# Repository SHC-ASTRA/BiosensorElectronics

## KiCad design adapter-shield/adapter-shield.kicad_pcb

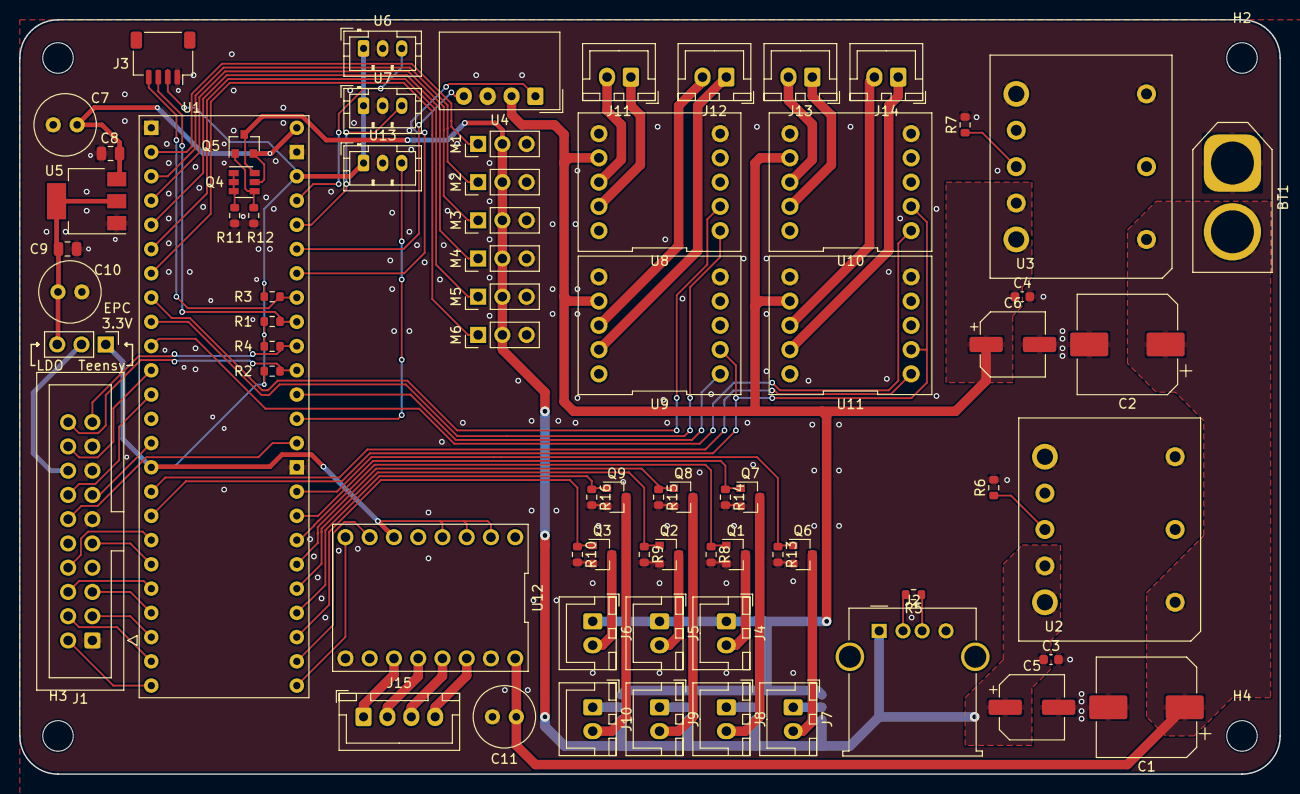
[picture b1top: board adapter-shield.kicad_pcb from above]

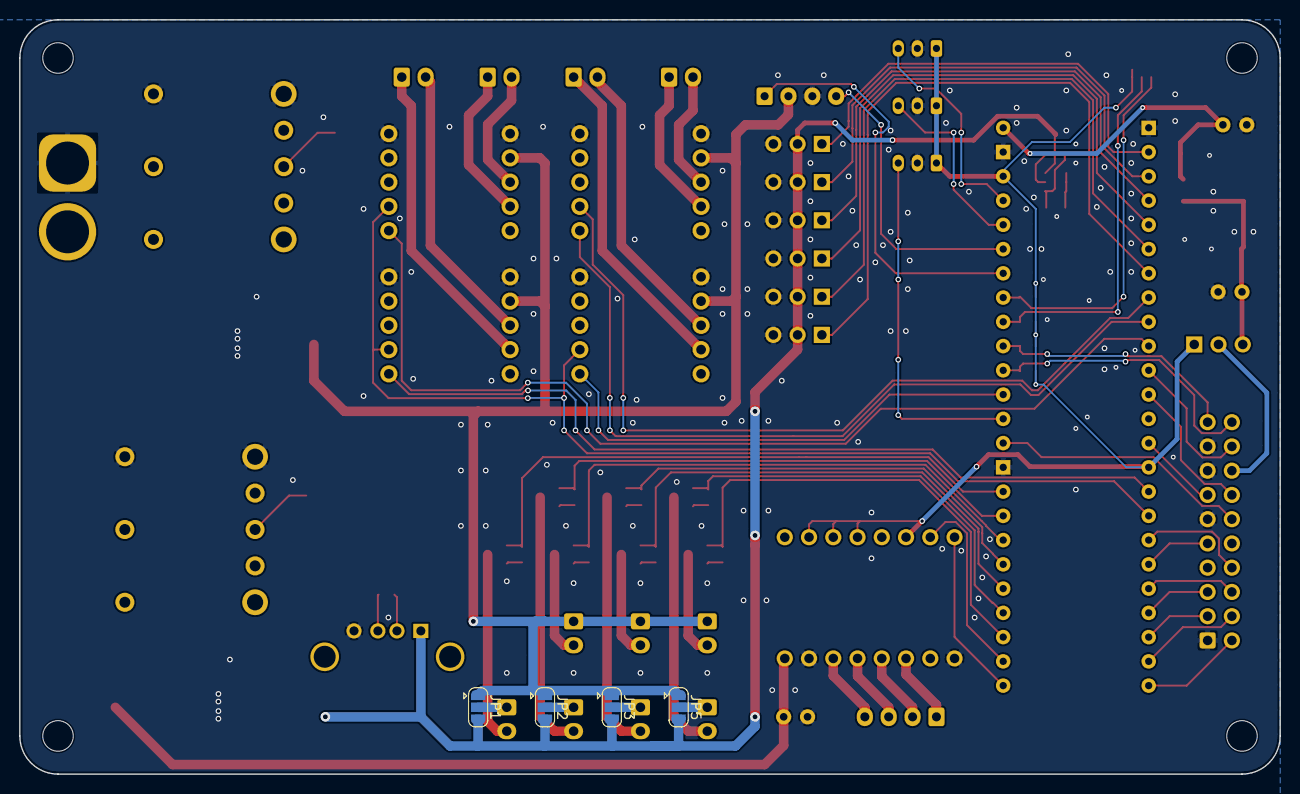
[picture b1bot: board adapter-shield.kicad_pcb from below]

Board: 2 copper layers, 132.0 x 79.0 mm, 80 parts (4 on the bottom side), 78 nets.

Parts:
BT1: XT60_Battery_Connector; AMASS_XT60-M_1x02_P7.20mm_Vertical
C1, C2: 33u; CP_Elec_10x10
C3, C4: 0.1u; C_0603_1608Metric
C5, C6: 22u; CP_Elec_6.3x5.9
C7, C10, C11: 100uF; C_Radial_D6.3mm_H7.0mm_P2.50mm
C8, C9: 1uF; C_0805_2012Metric
H1, H2, H3, H4: MountingHole; MountingHole_3.2mm_M3
J1: Camera; IDC-Header_2x10_P2.54mm_Vertical
J2: USB_A; USB_A_Molex_67643_Horizontal
J3: QWIIC_Generic_Conn; JST_SH_SM04B-SRSS-TB_1x04-1MP_P1.00mm_Horizontal
J4, J5, J6, J7, J8, J9, J10, J11, J12, J13, J14: Conn_01x02; JST_XH_B2B-XH-A_1x02_P2.50mm_Vertical
J15: Conn_01x04; JST_XH_B4B-XH-A_1x04_P2.50mm_Vertical
JP1, JP2, JP3, JP5: SolderJumper_3_Open; SolderJumper-3_P1.3mm_Open_RoundedPad1.0x1.5mm
JP4: Jumper; PinHeader_1x03_P2.54mm_Vertical
M1, M2, M3, M4, M5, M6: Motor_Servo; PinHeader_1x03_P2.54mm_Vertical
Q1, Q2, Q3, Q6, Q7, Q8, Q9: Q_NMOS_GSD; SOT-23
Q4: Q_DUAL_PNP_PNP_C1B1B2C2E2E1; SOT-23-6
Q5: Q_PMOS_GSD; SOT-23
R1, R2, R3, R4, R8, R9, R10, R11, R13, R14, R15, R16: 10k; R_0603_1608Metric
R5: 200; R_0603_1608Metric
R6: 8.45k; R_0603_1608Metric
R7: 1.82k; R_0603_1608Metric
R12: 47k; R_0603_1608Metric
U1: Teensy_4.1; Teensy4.1
U2, U3: TDK_I3A4W008A033V; Power_Supply_32nd_Brick
U4: LynxServo; Molex_SPOX_5268-04A_1x04_P2.50mm_Horizontal
U5: 3.3V LDO; SOT-223-3_TabPin2
U6, U7, U13: AH1815-P-B; JST_PH_B3B-PH-K_1x03_P2.00mm_Vertical
U8, U9, U10, U11: MAX14870_Breakout; Pololu_2961
U12: Pololu_Compact_TB67S249FTG; DIP-16_500

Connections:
+3V3: J3.2, JP4.1, R1.1, R2.1, R3.1, R4.1, U1.15, U1.28, U6.1, U7.1, U12.2, U12.3, U12.4, U12.6, U13.1
+5V: C7.1, C8.1, Q4.5, Q5.2, U1.30, U5.3
+5VP: C3.1, C5.1, J2.1, JP1.3, JP2.3, JP3.3, JP5.3, M1.2, M2.2, M3.2, M4.2, M5.2, M6.2, Q4.6, Q5.3, U2.7, U2.8
+12V: C4.1, C6.1, J4.1, J5.1, J6.1, JP1.1, JP2.1, JP3.1, JP5.1, U3.7, U3.8, U4.2, U8.7, U9.7, U10.7, U11.7
/ADC_CLK: J1.12, U1.17
/ADC_CS: J1.14, U1.12
/ADC_DATA: J1.13, U1.14
/Act_DIR: U1.8, U8.2
/Act_PWM: U1.9, U8.1
/CLR_DATA: J1.4, U1.38
/CLR_PIX: J1.6, U1.35
/DATA_RDY: J1.3, U1.37
/FAN1: Q1.1, R8.1, U1.46
/FAN2: Q2.1, R9.1, U1.44
/FAN3: Q3.1, R10.1, U1.42
/GEN1: Q7.1, R14.1, U1.47
/GEN2: Q8.1, R15.1, U1.45
/GEN3: Q9.1, R16.1, U1.43
/Hall_SW_1: U1.27, U6.3
/Hall_SW_2: U1.26, U7.3
/Hall_SW_3: U1.18, U13.3
/LIGHT: Q6.1, R13.1, U1.48
/Lynx_RX: U1.24, U4.1
/Lynx_TX: U1.25, U4.4
/M1_PWM: M1.1, U1.2
/M2_PWM: M2.1, U1.3
/M3_PWM: M3.1, U1.4
/M4_PWM: M4.1, U1.5
/M5_PWM: M5.1, U1.6
/M6_PWM: M6.1, U1.7
/PWR_DOWN: J1.2, U1.39
/Pump1_PWM: U1.19, U9.1
/Pump2_PWM: U1.10, U10.1
/Pump3_PWM: U1.31, U11.1
/Pump_DIR: U1.32, U9.2, U10.2, U11.2
/QWIIC_SCL: J3.4, R3.2, U1.23
/QWIIC_SDA: J3.3, R1.2, U1.22
/READ: J1.18, U1.11
/SCL: J1.20, R2.2, U1.20
/SDA: J1.19, R4.2, U1.21
/SHUTTER: J1.5, U1.36
/STEP_DIR: U1.40, U12.8
/STEP_STEP: U1.41, U12.7
/VCC_3V3: J1.16, JP4.2
/VIDEO_N: J1.9, U1.34
/VIDEO_P: J1.8, U1.33
/V_BAT: BT1.2, C1.1, C2.1, C11.1, U2.1, U3.1, U12.16
GND: BT1.1, C1.2, C2.2, C3.2, C4.2, C5.2, C6.2, C7.2, C8.2, C9.2, C10.2, C11.2, J1.1, J1.11, J1.15, J1.17, J2.4, J3.1, M1.3, M2.3, M3.3, M4.3, M5.3, M6.3, Q1.2, Q2.2, Q3.2, Q6.2, Q7.2, Q8.2, Q9.2, R6.2, R7.2, R8.2, R9.2, R10.2, R11.2, R12.2, R13.2, R14.2, R15.2, R16.2, U1.1, U1.16, U1.29, U2.3, U2.4, U3.3, U3.4, U4.3, U5.1, U6.2, U7.2, U8.5, U8.6, U9.5, U9.6, U10.5, U10.6, U11.5, U11.6, U12.9, U12.15, U13.2
unnamed: C9.1, C10.1, JP4.3, U5.2
unnamed: J2.2, R5.2
unnamed: J2.3, R5.1
unnamed: J4.2, Q1.3
unnamed: J5.2, Q2.3
unnamed: J6.2, Q3.3
unnamed: J7.1, JP1.2
unnamed: J7.2, Q6.3
unnamed: J8.1, JP2.2
unnamed: J8.2, Q7.3
unnamed: J9.1, JP3.2
unnamed: J9.2, Q8.3
unnamed: J10.1, JP5.2
unnamed: J10.2, Q9.3
unnamed: J11.1, U8.9
unnamed: J11.2, U8.8
unnamed: J12.1, U9.9
unnamed: J12.2, U9.8
unnamed: J13.1, U10.9
unnamed: J13.2, U10.8
unnamed: J14.1, U11.9
unnamed: J14.2, U11.8
unnamed: J15.1, U12.11
unnamed: J15.2, U12.12
unnamed: J15.3, U12.13
unnamed: J15.4, U12.14
unnamed: Q4.1, Q4.2, Q4.3, R11.1
unnamed: Q4.4, Q5.1, R12.1
unnamed: R6.1, U2.6
unnamed: R7.1, U3.6

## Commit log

2021-09-20 Finished Schematic
2021-09-21 Part nums and footprints
2021-09-21 Started PCB
2021-09-21 DONE (please)
2021-09-22 Added info
2022-04-13 started on V2
2022-04-14 PCB Layout
2022-04-15 Finished PCB

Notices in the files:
adapter-shield/adapter-shield.kicad_pcb:
(C)2020 Adrian Studer
CERN Open Hardware Licence Version 2 - Permissive
